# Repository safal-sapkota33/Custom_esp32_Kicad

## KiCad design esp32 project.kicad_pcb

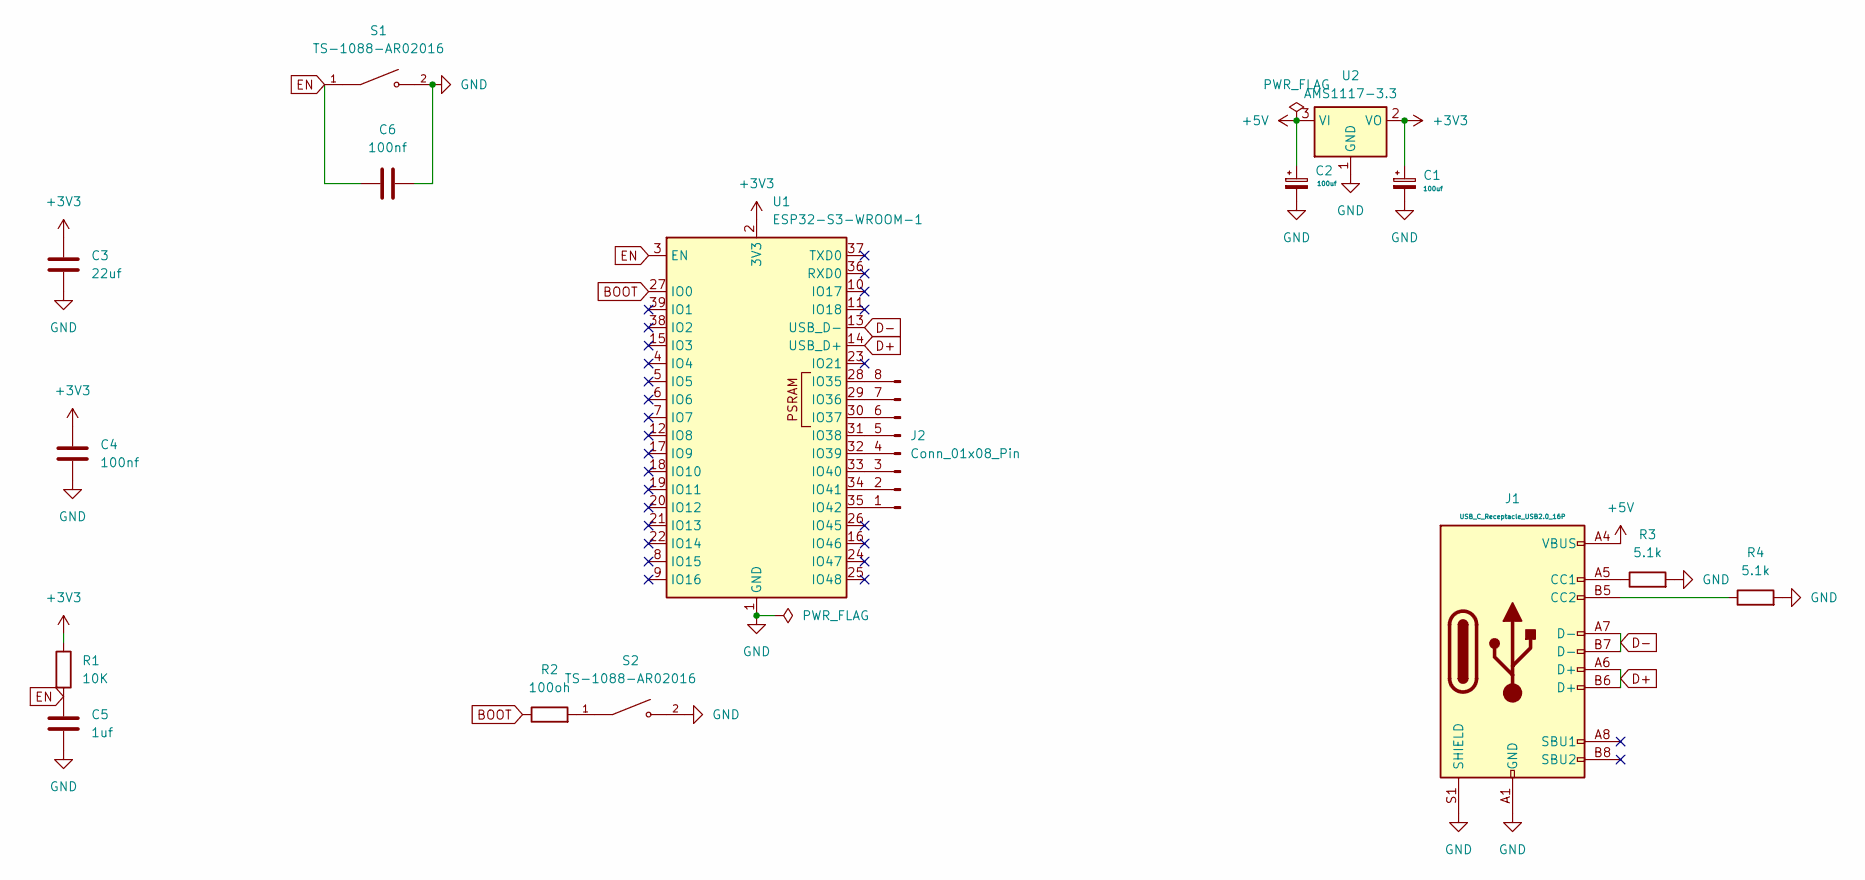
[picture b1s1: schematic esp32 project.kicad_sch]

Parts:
C1, C2: 100uf; CP_EIA-3528-21_Kemet-B_HandSolder
C3: 22uf; C_0805_2012Metric_Pad1.18x1.45mm_HandSolder
C4, C6: 100nf; C_0805_2012Metric_Pad1.18x1.45mm_HandSolder
C5: 1uf; C_0805_2012Metric_Pad1.18x1.45mm_HandSolder
J1: USB_C_Receptacle_USB2.0_16P; USB_C_Receptacle_GCT_USB4105-xx-A_16P_TopMnt_Horizontal
J2: Conn_01x08_Pin; PinHeader_1x08_P1.00mm_Vertical
R1: 10K; R_0805_2012Metric
R2: 100oh; R_0805_2012Metric
R3, R4: 5.1k; R_0805_2012Metric
S1, S2: TS-1088-AR02016; SW_TS-1088-AR02016; PARTREV N/A
U1: ESP32-S3-WROOM-1
U2: AMS1117-3.3; SOT-223-3_TabPin2

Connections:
+3V3: C1.1, C3.1, C4.1, R1.1, U1.2 (3V3), U2.2 (VO)
+5V: C2.1, J1.A4 (VBUS), J1.A9 (VBUS), J1.B4 (VBUS), J1.B9 (VBUS), U2.3 (VI)
BOOT: R2.1, U1.27 (IO0)
D+: J1.A6 (D+), J1.B6 (D+), U1.14 (USB_D+)
D-: J1.A7 (D-), J1.B7 (D-), U1.13 (USB_D-)
EN: C5.2, C6.2, R1.2, S1.1, U1.3 (EN)
GND: C1.2, C2.2, C3.2, C4.2, C5.1, C6.1, J1.A1 (GND), J1.A12 (GND), J1.B1 (GND), J1.B12 (GND), J1.S1 (SHIELD), R3.2, R4.2, S1.2, S2.2, U1.1 (GND), U1.40 (GND), U1.41 (GND), U2.1 (GND)
unnamed: J1.A5 (CC1), R3.1
unnamed: J1.B5 (CC2), R4.1
unnamed: J2.1, U1.35 (IO42)
unnamed: J2.2, U1.34 (IO41)
unnamed: J2.3, U1.33 (IO40)
unnamed: J2.4, U1.32 (IO39)
unnamed: J2.5, U1.31 (IO38)
unnamed: J2.6, U1.30 (IO37)
unnamed: J2.7, U1.29 (IO36)
unnamed: J2.8, U1.28 (IO35)
unnamed: R2.2, S2.1

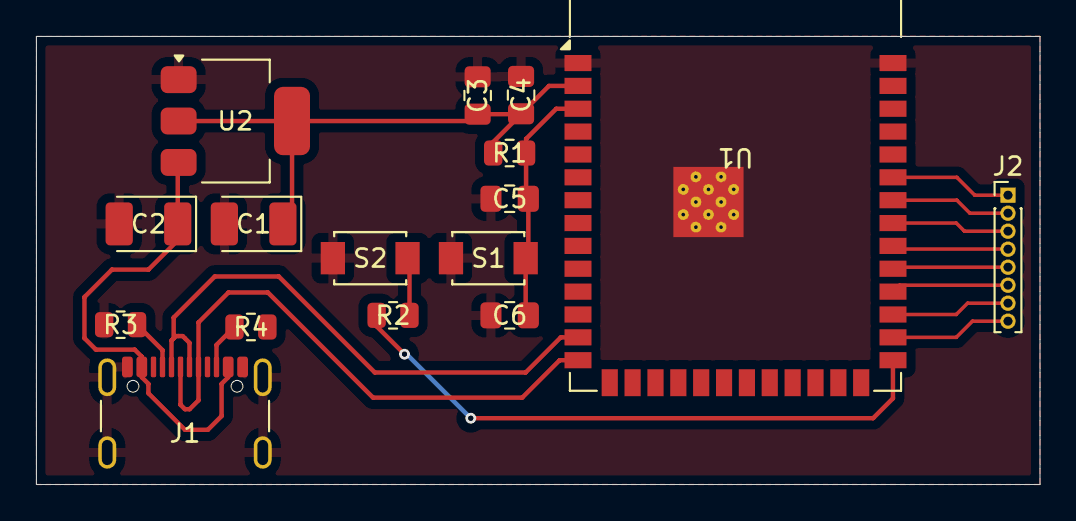
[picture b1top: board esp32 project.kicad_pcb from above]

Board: 2 copper layers, 55.8 x 24.9 mm, 16 parts (0 on the bottom side), 18 nets.
